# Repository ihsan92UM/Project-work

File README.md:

# Project-work

## Repository Structure
```
Project-work/
├── Graphics/
│   └── Contains all .png used in Markdown files
├── PCB Designs/
│   └── Contains KiCAD files and final JLCPCB Gerber files
├── Programming Guides/
│   └── Contails First-Time Programming setup for DK and Custom Boards
├── STM32U5_codes/
│   └── v1 and v2 Custom Board Codes
└── nRF5340_codes/
    └── nRF5340DK code and Final Custom Board Code

```

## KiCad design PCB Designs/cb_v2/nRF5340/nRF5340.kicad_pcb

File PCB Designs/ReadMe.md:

# PCB Design 

## Repository Structure
```
PCB Designs/
├── JLCPCB_Files/
│   ├── Stencil
│   ├── board1_nrf5340
│   ├── board2_stm32
│   ├── Stencil.zip
│   ├── board1_nrf5340.zip
│   └── board2_stm32.zip	
├── cb_v1/
│   ├── STM32U5
│   └── nRF5340	
├── cb_v2/
│   ├── STM32U5
│   └── nRF5340	
├── Parts_list.xlsx
└── pcb ordering JLCPCB.pdf
```
## Requirement

* [KiCAD 8.0](https://www.kicad.org/download/)

## Production House
* [JLCPCB](https://jlcpcb.com/)
>[!NOTE]
> Follow the [PDF](https://github.com/ihsan92UM/Project-work/blob/359b432a75f67255255755fd50f5ba6b127fc0ec/PCB%20Designs/pcb%20ordering%20JLCPCB.pdf) for ordering manual. Both Custom board uses recomended stackup for 1.6mm diameter with Impedence control.

## Folder Deatils
| Folder | Comments     |
|------------------------------|------------------------------|
|  JLCPCB_Files                    | .zip files are Production files for JLCPCB           |
| cb_v1                 | Sensor Measurement Board (60mm Diameter )          |
| cb_v2          |   Final Custom Board files |
| Parts_list.xlsx                | Remaining components           |

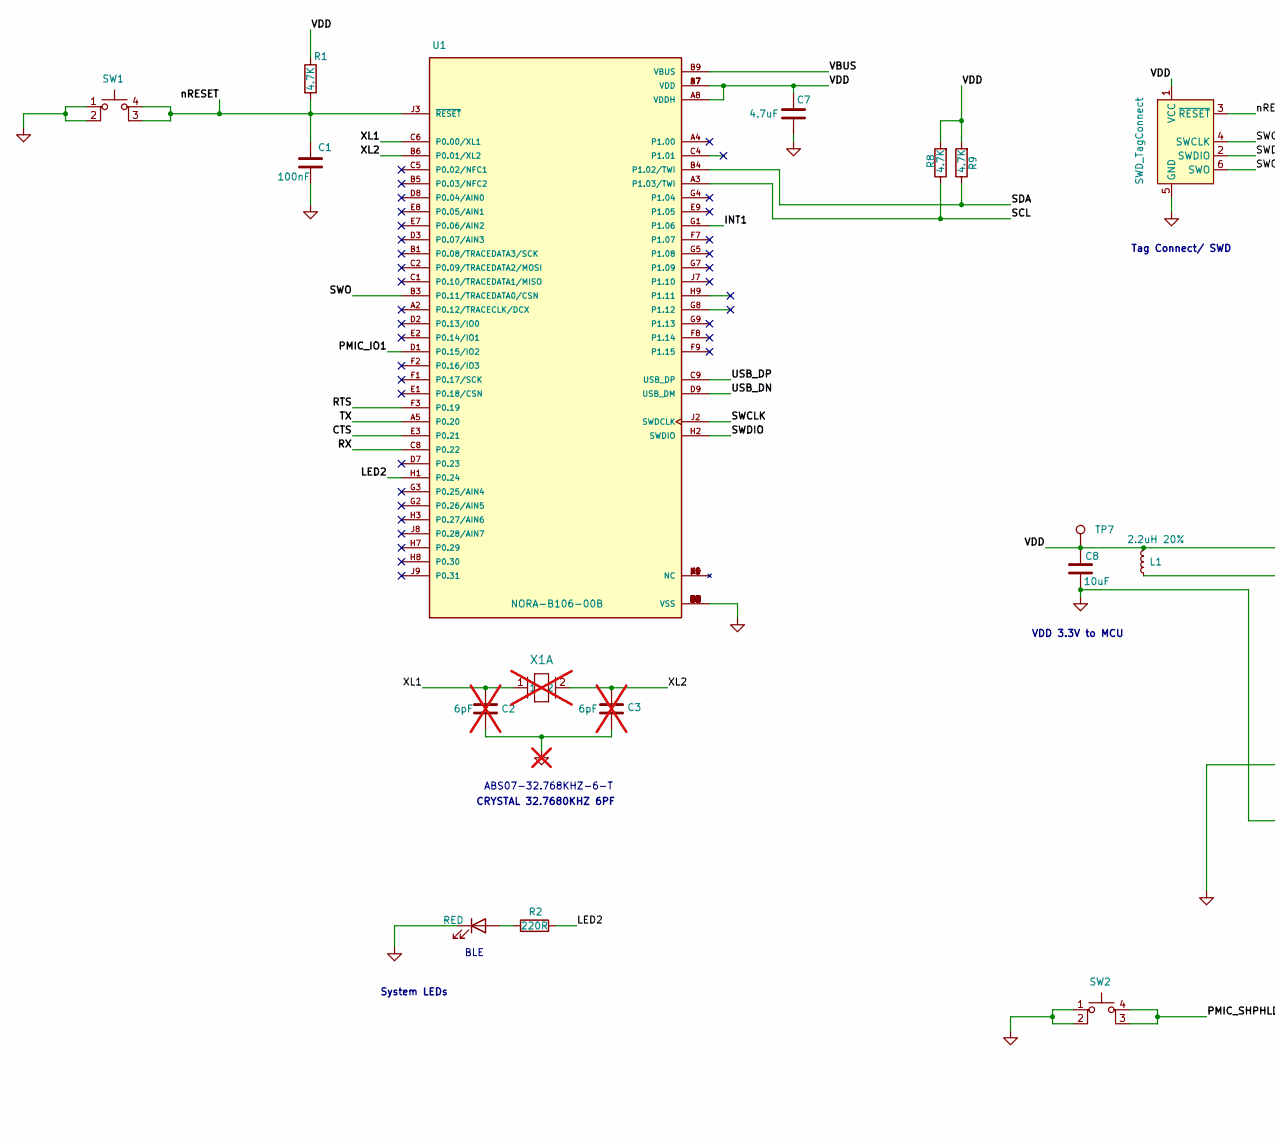
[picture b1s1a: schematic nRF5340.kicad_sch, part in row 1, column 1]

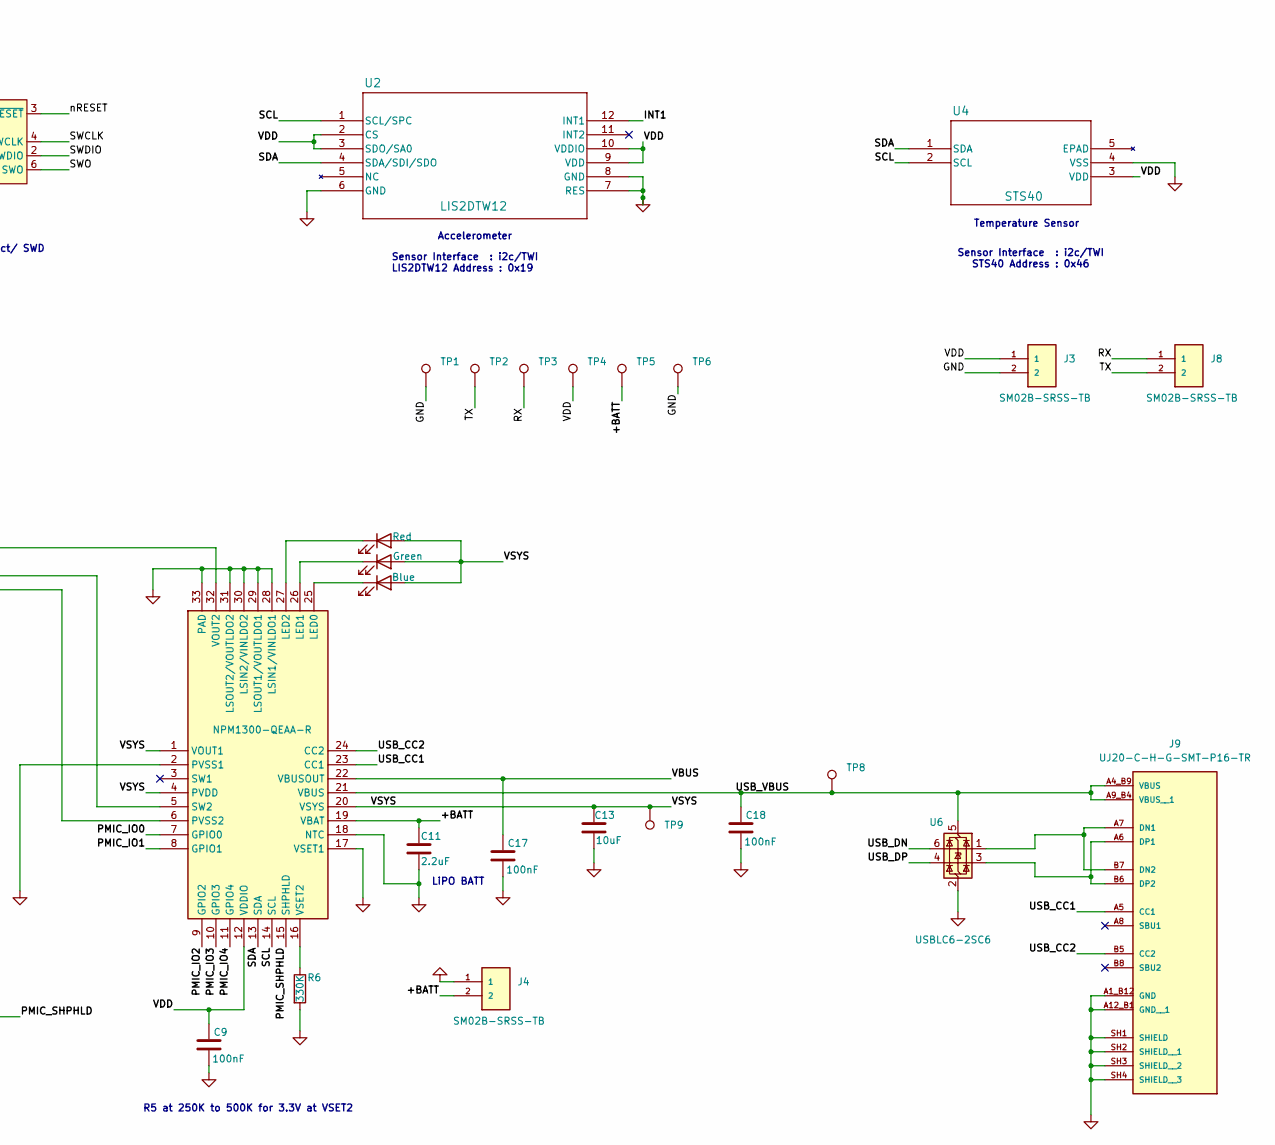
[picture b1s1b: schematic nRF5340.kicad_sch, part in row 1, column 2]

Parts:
C1, C9, C17, C18: 100nF; C_0603_1608Metric
C2, C3: 6pF; C_0603_1608Metric; not fitted
C7: 4.7uF; C_0603_1608Metric
C8, C13: 10uF; C_0603_1608Metric
C11: 2.2uF; C_0603_1608Metric
D1: RED; LED_0603_1608Metric
D3: Red; LED_0603_1608Metric
D4: Green; LED_0603_1608Metric
D5: Blue; LED_0603_1608Metric
IC1: NPM1300-QEAA-R; NPM1300; Manufacturer_Part_Number NPM1300-QEAA-R; Mouser Part Number 949-NPM1300-QEAA-R
J2: SWD_TagConnect; Tag-Connect_TC2030-IDC-NL_2x03_P1.27mm_Vertical
J3, J4, J8: SM02B-SRSS-TB
J9: UJ20-C-H-G-SMT-P16-TR; SAMESKY_UJ20-C-H-G-SMT-P16-TR-USBC-FEMALE; PARTREV 1.0
L1: 2.2uH 20%; L_0603_1608Metric
R1, R8, R9: 4.7K; R_0603_1608Metric
R2: 220R; R_0603_1608Metric
R6: 330K; R_0603_1608Metric
SW1, SW2: SW_MEC_5E; SW4_PTS815 SJM 250 SMTR LFS_CNK
TP1, TP2, TP3, TP4, TP5, TP6: TestPoint; TestPoint_Pad_1.5x1.5mm
TP7, TP9: TestPoint; TestPoint_Pad_D1.0mm
TP8: TestPoint; TestPoint_Pad_D1.5mm
U1: NORA-B106-00B; PARTREV R05
U2: LIS2DTW12; LIS2DTW12_STM
U4: STS40
U6: USBLC6-2SC6; SOT-23-6
X1: ABS07-32.768KHZ-6-T; XTAL_ABS07_ABR; not fitted

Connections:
/+BATT: C11.1, IC1.19 (VBAT), J4.2, TP5.1
/CTS: U1.E3 (P0.21)
/INT1: U1.G1 (P1.06), U2.12 (INT1)
/LED2: R2.2, U1.H1 (P0.24)
/PMIC_IO0: IC1.7 (GPIO0)
/PMIC_IO1: IC1.8 (GPIO1), U1.D1 (P0.15/IO2)
/PMIC_IO2: IC1.9 (GPIO2)
/PMIC_IO3: IC1.10 (GPIO3)
/PMIC_IO4: IC1.11 (GPIO4)
/PMIC_SHPHLD: IC1.15 (SHPHLD), SW2.3 (K), SW2.4 (A)
/RTS: U1.F3 (P0.19)
/RX: J8.1, TP3.1, U1.C8 (P0.22)
/SCL: IC1.14 (SCL), R8.1, U1.A3 (P1.03/TWI), U2.1 (SCL/SPC), U4.2 (SCL)
/SDA: IC1.13 (SDA), R9.1, U1.B4 (P1.02/TWI), U2.4 (SDA/SDI/SDO), U4.1 (SDA)
/SWCLK: J2.4 (SWCLK), U1.J2 (SWDCLK)
/SWDIO: J2.2 (SWDIO), U1.H2 (SWDIO)
/SWO: J2.6 (SWO), U1.B3 (P0.11/TRACEDATA0/CSN)
/TX: J8.2, TP2.1, U1.A5 (P0.20)
/USB_CC1: IC1.23 (CC1), J9.A5 (CC1)
/USB_CC2: IC1.24 (CC2), J9.B5 (CC2)
/USB_DN: U1.D9 (USB_DM), U6.6 (I/O1)
/USB_DP: U1.C9 (USB_DP), U6.4 (I/O2)
/USB_VBUS: C18.1, IC1.21 (VBUS), J9.A4_B9 (VBUS), J9.A9_B4 (VBUS__1), TP8.1, U6.5 (VBUS)
/VBUS: C17.1, IC1.22 (VBUSOUT), U1.B9 (VBUS)
/VDD: C7.1, C8.1, C9.1, IC1.12 (VDDIO), IC1.32 (VOUT2), J2.1 (VCC), J3.1, L1.2, R1.1, R8.2, R9.2, TP4.1, TP7.1, U1.A7 (VDD), U1.A8 (VDDH), U1.B7 (VDD), U2.2 (CS), U2.3 (SDO/SA0), U2.9 (VDD), U2.10 (VDDIO), U4.3 (VDD)
/VSYS: C13.1, D3.2 (A), D4.2 (A), D5.2 (A), IC1.1 (VOUT1), IC1.4 (PVDD), IC1.20 (VSYS), TP9.1
/XL1: C2.1, U1.C6 (P0.00/XL1), X1.1
/XL2: C3.1, U1.B6 (P0.01/XL2), X1.2
/nRESET: C1.1, J2.3 (~RESET), R1.2, SW1.3 (K), SW1.4 (A), U1.J3 (~RESET)
GND: C1.2, C2.2, C3.2, C7.2, C8.2, C9.2, C11.2, C13.2, C17.2, C18.2, D1.1 (K), IC1.2 (PVSS1), IC1.6 (PVSS2), IC1.17 (VSET1), IC1.18 (NTC), IC1.28 (LSIN1/VINLDO1), IC1.29 (LSOUT1/VOUTLDO1), IC1.30 (LSIN2/VINLDO2), IC1.31 (LSOUT2/VOUTLDO2), IC1.33 (PAD), J2.5 (GND), J3.2, J4.1, J9.A1_B12 (GND), J9.A12_B1 (GND__1), J9.SH1 (SHIELD), J9.SH2 (SHIELD__1), J9.SH3 (SHIELD__2), J9.SH4 (SHIELD__3), R6.2, SW1.1, SW1.2, SW2.1, SW2.2, TP1.1, TP6.1, U1.A1 (VSS), U1.A9 (VSS), U1.B2 (VSS), U1.B8 (VSS), U1.E4 (VSS), U1.E5 (VSS), U1.F4 (VSS), U1.F5 (VSS), U1.K2 (VSS), U1.K3 (VSS), U1.K5 (VSS), U1.K7 (VSS), U1.K8 (VSS), U1.L1 (VSS), U1.L9 (VSS), U1.M1 (VSS), U1.M2 (VSS), U1.M8 (VSS), U1.M9 (VSS), U2.6 (GND), U2.7 (RES), U2.8 (GND), U4.4 (VSS), U6.2 (GND)
unnamed: D1.2 (A), R2.1
unnamed: D3.1 (K), IC1.27 (LED2)
unnamed: D4.1 (K), IC1.26 (LED1)
unnamed: D5.1 (K), IC1.25 (LED0)
unnamed: IC1.5 (SW2), L1.1
unnamed: IC1.16 (VSET2), R6.1
unnamed: J9.A7 (DN1), J9.B7 (DN2), U6.1 (I/O1)
unnamed: J9.A6 (DP1), J9.B6 (DP2), U6.3 (I/O2)

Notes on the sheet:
Sensor Interface : i2c/TWI STS40 Address : 0x46
Sensor Interface : i2c/TWI LIS2DTW12 Address : 0x19
LiPO BATT
BLE
Tag Connect/ SWD
CRYSTAL 32.7680KHZ 6PF
Temperature Sensor
System LEDs
R5 at 250K to 500K for 3.3V at VSET2
Accelerometer
ABS07-32.768KHZ-6-T
VDD 3.3V to MCU

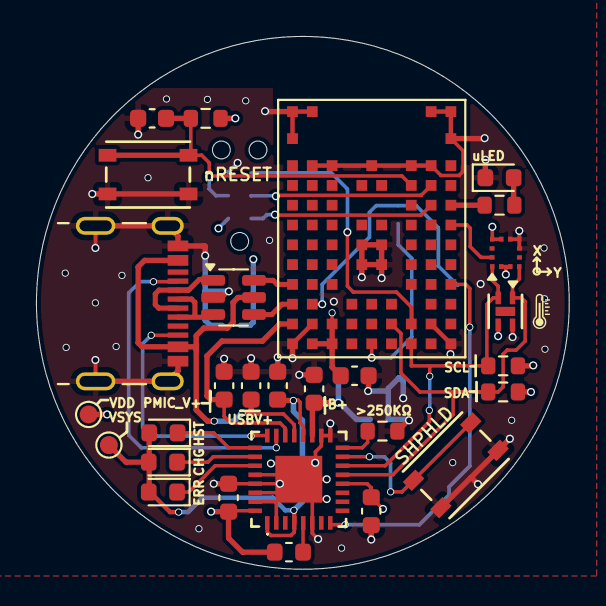
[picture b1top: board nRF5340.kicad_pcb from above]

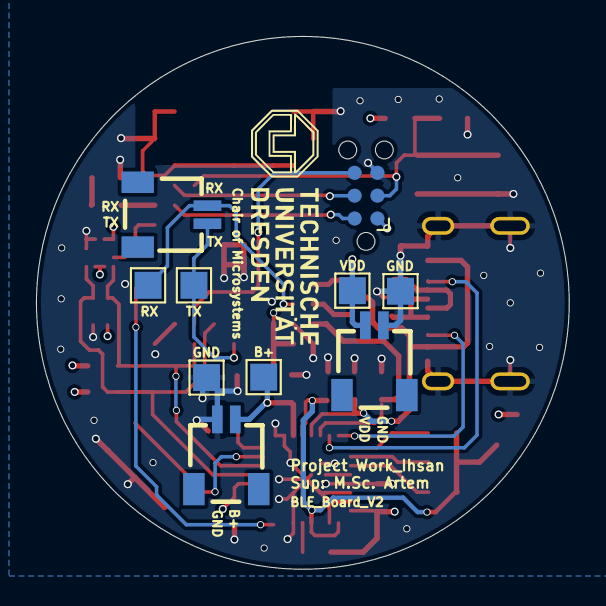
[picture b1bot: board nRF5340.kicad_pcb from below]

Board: 4 copper layers, 29.6 x 29.6 mm, 39 parts (11 on the bottom side), 30 nets.

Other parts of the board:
g: LOGO

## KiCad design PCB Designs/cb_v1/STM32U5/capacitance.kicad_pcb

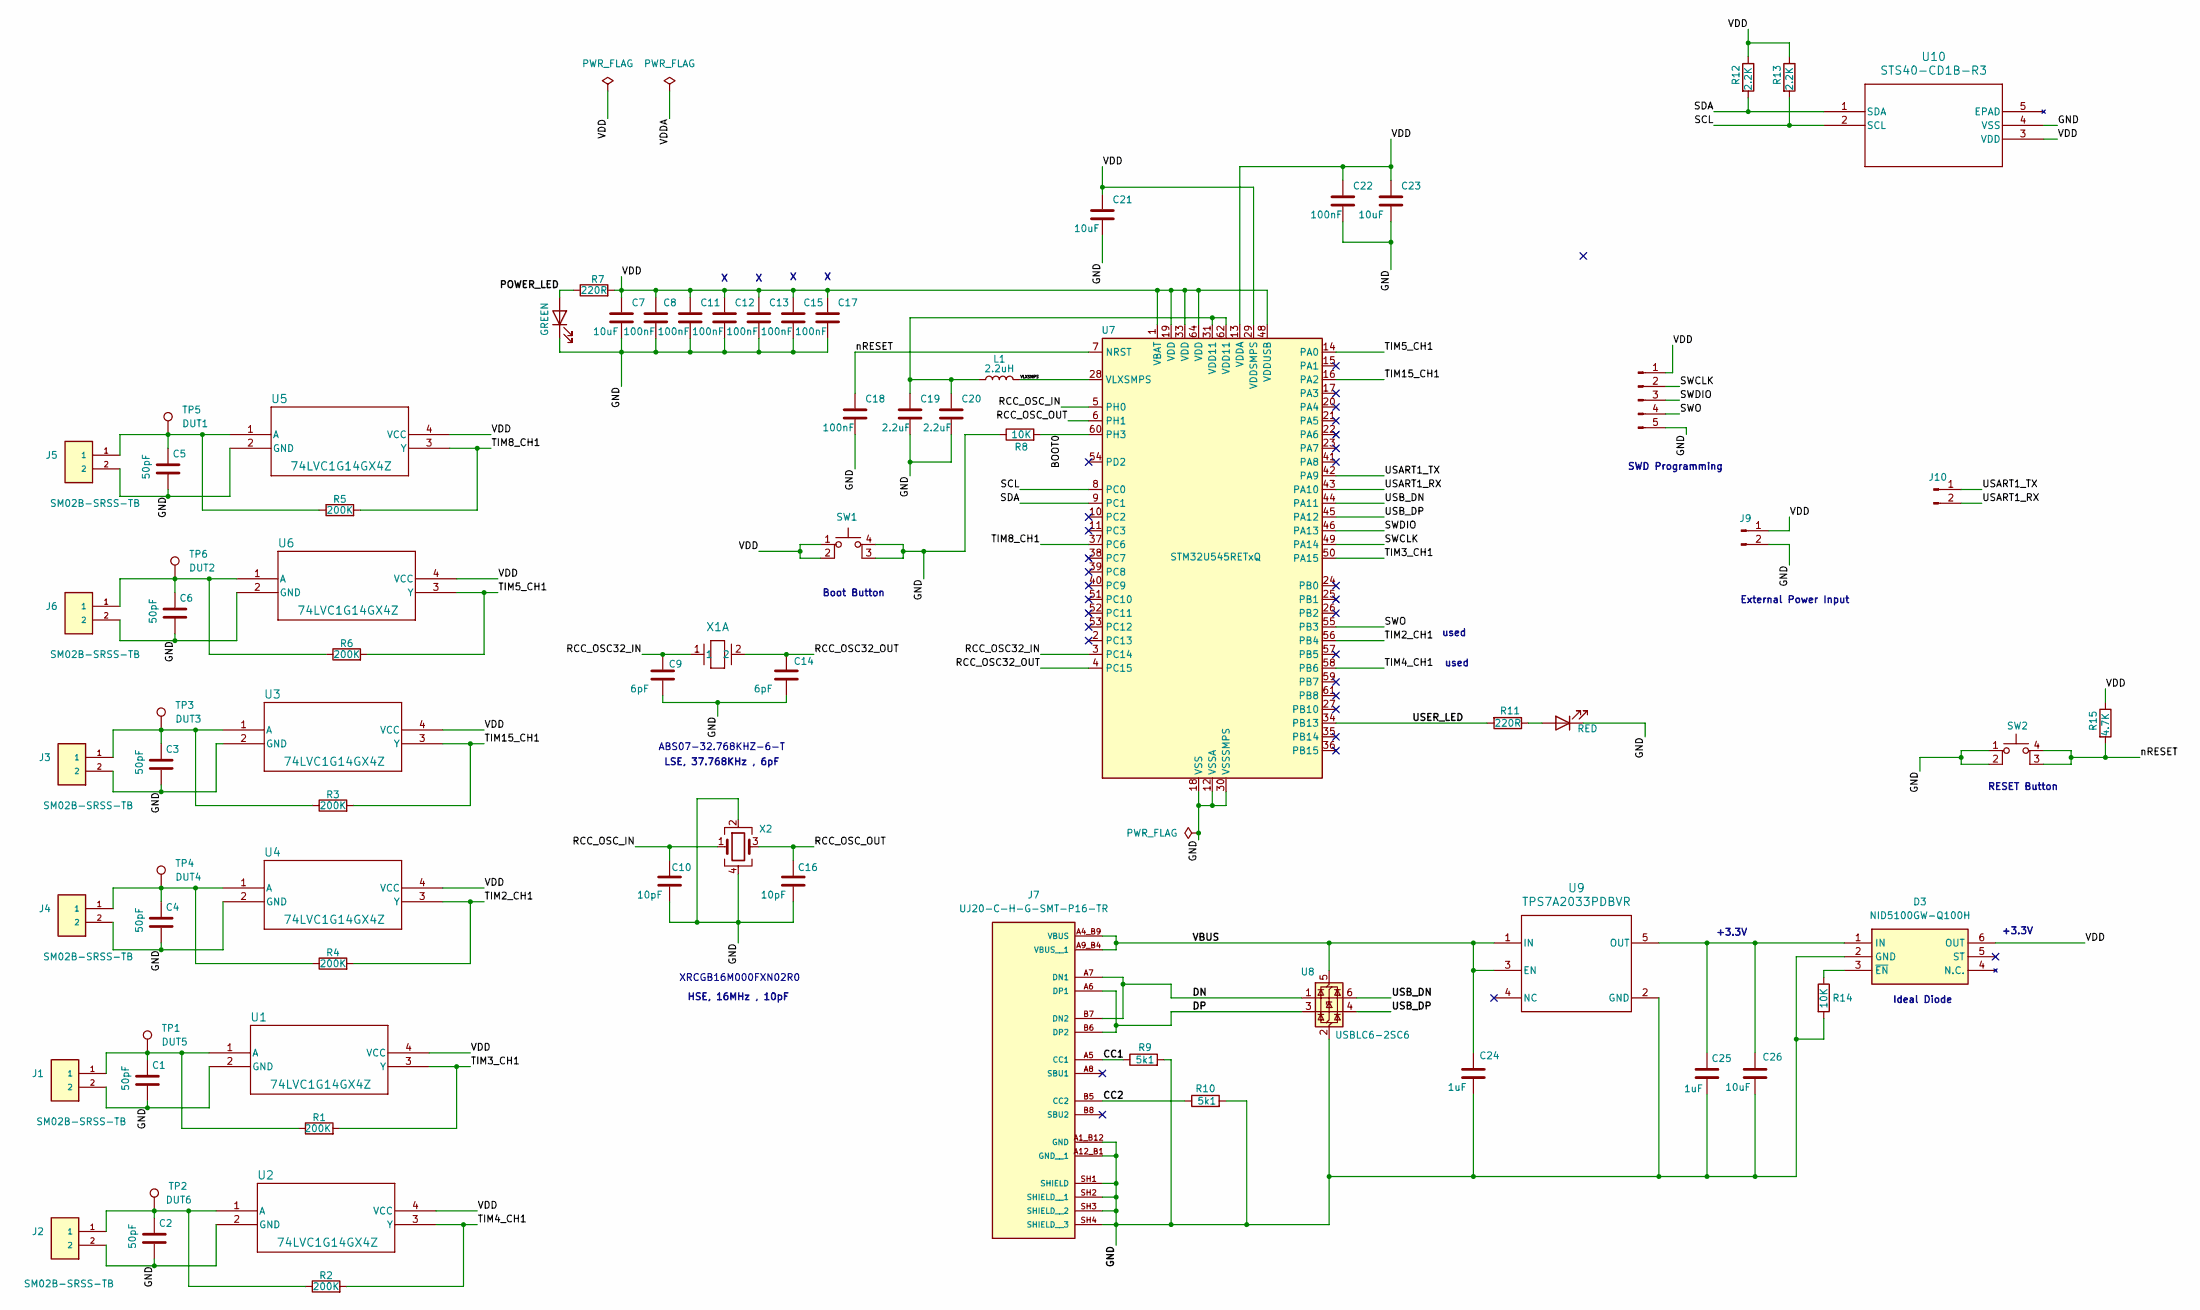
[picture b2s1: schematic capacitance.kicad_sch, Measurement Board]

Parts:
C1, C2, C3, C4, C5, C6: 50pF; C_0603_1608Metric
C7, C21, C23, C26: 10uF; C_0603_1608Metric
C8, C11, C12, C13, C15, C17, C18, C22: 100nF; C_0603_1608Metric
C9, C14: 6pF; C_0603_1608Metric
C10, C16: 10pF; C_0603_1608Metric
C19, C20: 2.2uF; C_0603_1608Metric
C24, C25: 1uF; C_0603_1608Metric
D1: GREEN; LED_0603_1608Metric
D2: RED; LED_0603_1608Metric
D3: NID5100GW-Q100H; SOT65P210X110-6N; Manufacturer_Part_Number NID5100GW-Q100H; Mouser Part Number 771-NID5100GW-Q100H
J1, J2, J3, J4, J5, J6: SM02B-SRSS-TB
J7: UJ20-C-H-G-SMT-P16-TR; SAMESKY_UJ20-C-H-G-SMT-P16-TR-USBC-FEMALE; PARTREV 1.0
J8: Conn_01x05_Pin; PinHeader_1x05_P2.54mm_Vertical
J9, J10: Conn_01x02_Pin; PinHeader_1x02_P2.54mm_Vertical
L1: 2.2uH; L_0603_1608Metric
R1, R2, R3, R4, R5, R6: 200K; R_0603_1608Metric
R7, R11: 220R; R_0603_1608Metric
R8, R14: 10K; R_0603_1608Metric
R9, R10: 5k1; R_0603_1608Metric
R12, R13: 2.2K; R_0603_1608Metric
R15: 4.7K; R_0603_1608Metric
SW1, SW2: SW_MEC_5E; SW4_PTS815 SJM 250 SMTR LFS_CNK
TP1: DUT5; TestPoint_Pad_1.0x1.0mm
TP2: DUT6; TestPoint_Pad_1.0x1.0mm
TP3: DUT3; TestPoint_Pad_1.0x1.0mm
TP4: DUT4; TestPoint_Pad_1.0x1.0mm
TP5: DUT1; TestPoint_Pad_1.0x1.0mm
TP6: DUT2; TestPoint_Pad_1.0x1.0mm
U1, U2, U3, U4, U5, U6: 74LVC1G14GX4Z; X2SON4XP6XP6_NEX
U7: STM32U545RETxQ; LQFP-64_10x10mm_P0.5mm
U8: USBLC6-2SC6; SOT-23-6
U9: TPS7A2033PDBVR
U10: STS40-CD1B-R3; STS40
X1: ABS07-32.768KHZ-6-T; XTAL_ABS07_ABR
X2: Crystal_GND24; ECS-25MHz_XTAL

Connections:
/BOOT0: R8.2, U7.60 (PH3)
/CC1: J7.A5 (CC1), R9.1
/CC2: J7.B5 (CC2), R10.1
/DN: J7.A7 (DN1), J7.B7 (DN2), U8.1 (I/O1)
/DP: J7.A6 (DP1), J7.B6 (DP2), U8.3 (I/O2)
/GND: C1.2, C2.2, C3.2, C4.2, C5.2, C6.2, C7.2, C8.2, C9.2, C10.2, C11.2, C12.2, C13.2, C14.2, C15.2, C16.2, C17.2, C18.2, C19.2, C20.2, C21.2, C22.2, C23.2, C24.2, C25.2, C26.2, D1.1 (K), D2.1 (K), D3.2 (GND), J1.2, J2.2, J3.2, J4.2, J5.2, J6.2, J7.A1_B12 (GND), J7.A12_B1 (GND__1), J7.SH1 (SHIELD), J7.SH2 (SHIELD__1), J7.SH3 (SHIELD__2), J7.SH4 (SHIELD__3), J8.5, J9.2, R8.1, R9.2, R10.2, R14.2, SW1.3 (K), SW1.4 (A), SW2.1, SW2.2, U1.2 (GND), U2.2 (GND), U3.2 (GND), U4.2 (GND), U5.2 (GND), U6.2 (GND), U7.12 (VSSA), U7.18 (VSS), U7.30 (VSSSMPS), U7.32 (VSS), U7.47 (VSS), U7.63 (VSS), U8.2 (GND), U9.2 (GND), U10.4 (VSS), X2.2, X2.4
/POWER_LED: D1.2 (A), R7.1
/RCC_OSC32_IN: C9.1, U7.3 (PC14), X1.1
/RCC_OSC32_OUT: C14.1, U7.4 (PC15), X1.2
/RCC_OSC_IN: C10.1, U7.5 (PH0), X2.1
/RCC_OSC_OUT: C16.1, U7.6 (PH1), X2.3
/SCL: R13.2, U7.8 (PC0), U10.2 (SCL)
/SDA: R12.2, U7.9 (PC1), U10.1 (SDA)
/SWCLK: J8.2, U7.49 (PA14)
/SWDIO: J8.3, U7.46 (PA13)
/SWO: J8.4, U7.55 (PB3)
/TIM2_CH1: R4.2, U4.3 (Y), U7.56 (PB4)
/TIM3_CH1: R1.2, U1.3 (Y), U7.50 (PA15)
/TIM4_CH1: R2.2, U2.3 (Y), U7.58 (PB6)
/TIM5_CH1: R6.2, U6.3 (Y), U7.14 (PA0)
/TIM8_CH1: R5.2, U5.3 (Y), U7.37 (PC6)
/TIM15_CH1: R3.2, U3.3 (Y), U7.16 (PA2)
/USART1_RX: J10.2, U7.43 (PA10)
/USART1_TX: J10.1, U7.42 (PA9)
/USB_DN: U7.44 (PA11), U8.6 (I/O1)
/USB_DP: U7.45 (PA12), U8.4 (I/O2)
/USER_LED: R11.2, U7.34 (PB13)
/VBUS: C24.1, J7.A4_B9 (VBUS), J7.A9_B4 (VBUS__1), U8.5 (VBUS), U9.1 (IN), U9.3 (EN)
/VDD: C7.1, C8.1, C11.1, C12.1, C13.1, C15.1, C17.1, C21.1, C22.1, C23.1, D3.6 (OUT), J8.1, J9.1, R7.2, R12.1, R13.1, R15.1, SW1.1, SW1.2, U1.4 (VCC), U2.4 (VCC), U3.4 (VCC), U4.4 (VCC), U5.4 (VCC), U6.4 (VCC), U7.1 (VBAT), U7.13 (VDDA), U7.19 (VDD), U7.29 (VDDSMPS), U7.33 (VDD), U7.48 (VDDUSB), U7.64 (VDD), U10.3 (VDD)
/VLXSMPS: L1.2, U7.28 (VLXSMPS)
/nRESET: C18.1, R15.2, SW2.3 (K), SW2.4 (A), U7.7 (NRST)
unnamed: C19.1, C20.1, L1.1, U7.31 (VDD11), U7.62 (VDD11)
unnamed: D2.2 (A), R11.1
unnamed: C25.1, C26.1, D3.1 (IN), U9.5 (OUT)
unnamed: D3.3 (~EN), R14.1
unnamed: C1.1, J1.1, R1.1, TP1.1, U1.1 (A)
unnamed: C2.1, J2.1, R2.1, TP2.1, U2.1 (A)
unnamed: C3.1, J3.1, R3.1, TP3.1, U3.1 (A)
unnamed: C4.1, J4.1, R4.1, TP4.1, U4.1 (A)
unnamed: C5.1, J5.1, R5.1, TP5.1, U5.1 (A)
unnamed: C6.1, J6.1, R6.1, TP6.1, U6.1 (A)

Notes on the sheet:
HSE, 16MHz , 10pF
External Power Input
used
SWD Programming
+3.3V
Ideal Diode
LSE, 37.768KHz , 6pF
XRCGB16M000FXN02R0
Boot Button
RESET Button
ABS07-32.768KHZ-6-T

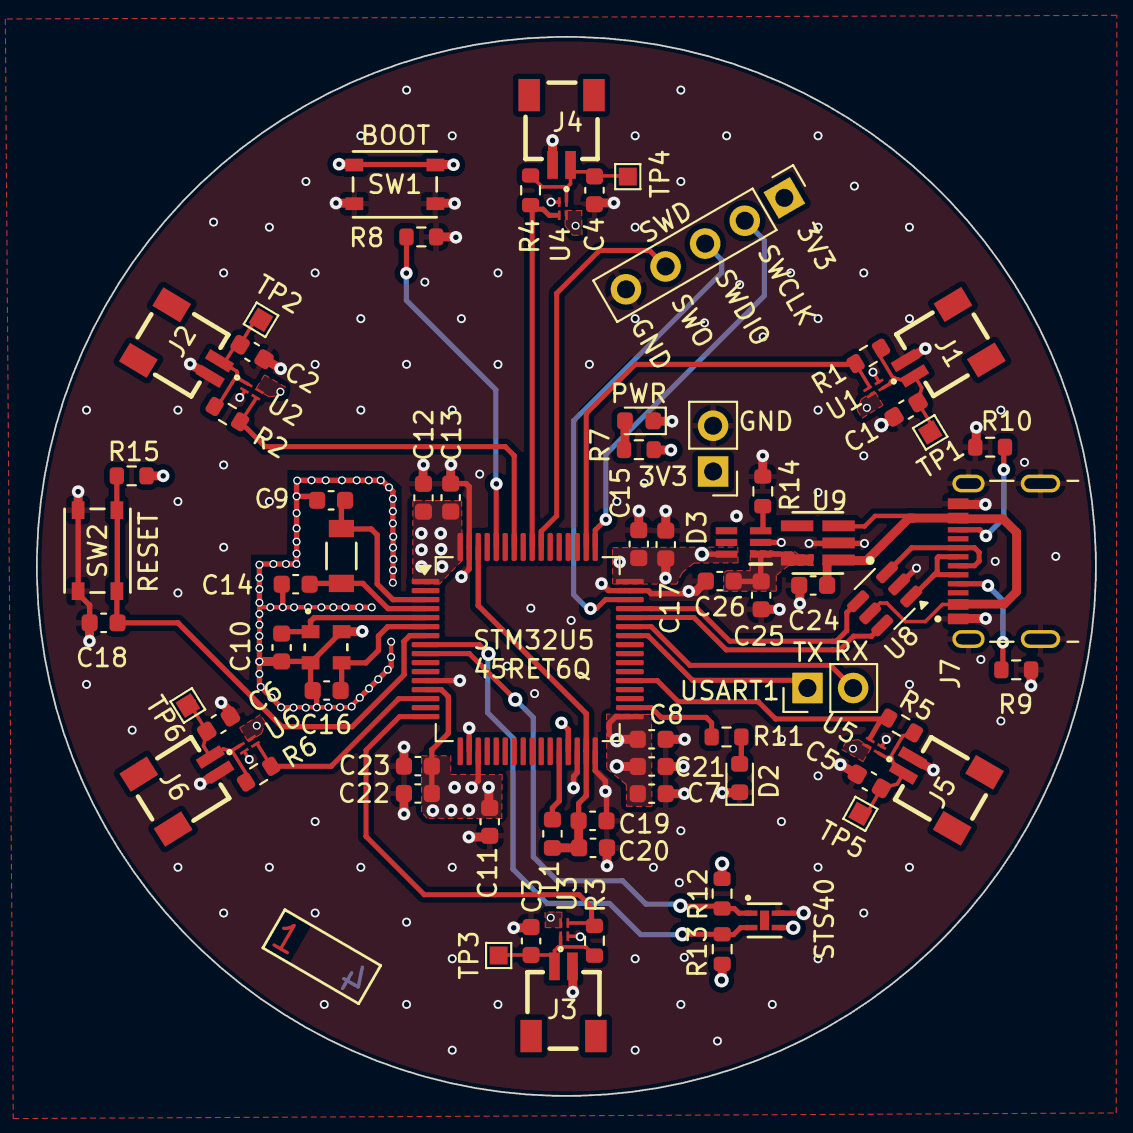
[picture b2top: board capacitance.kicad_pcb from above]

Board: 4 copper layers, 58.8 x 58.8 mm, 75 parts (0 on the bottom side), 41 nets.

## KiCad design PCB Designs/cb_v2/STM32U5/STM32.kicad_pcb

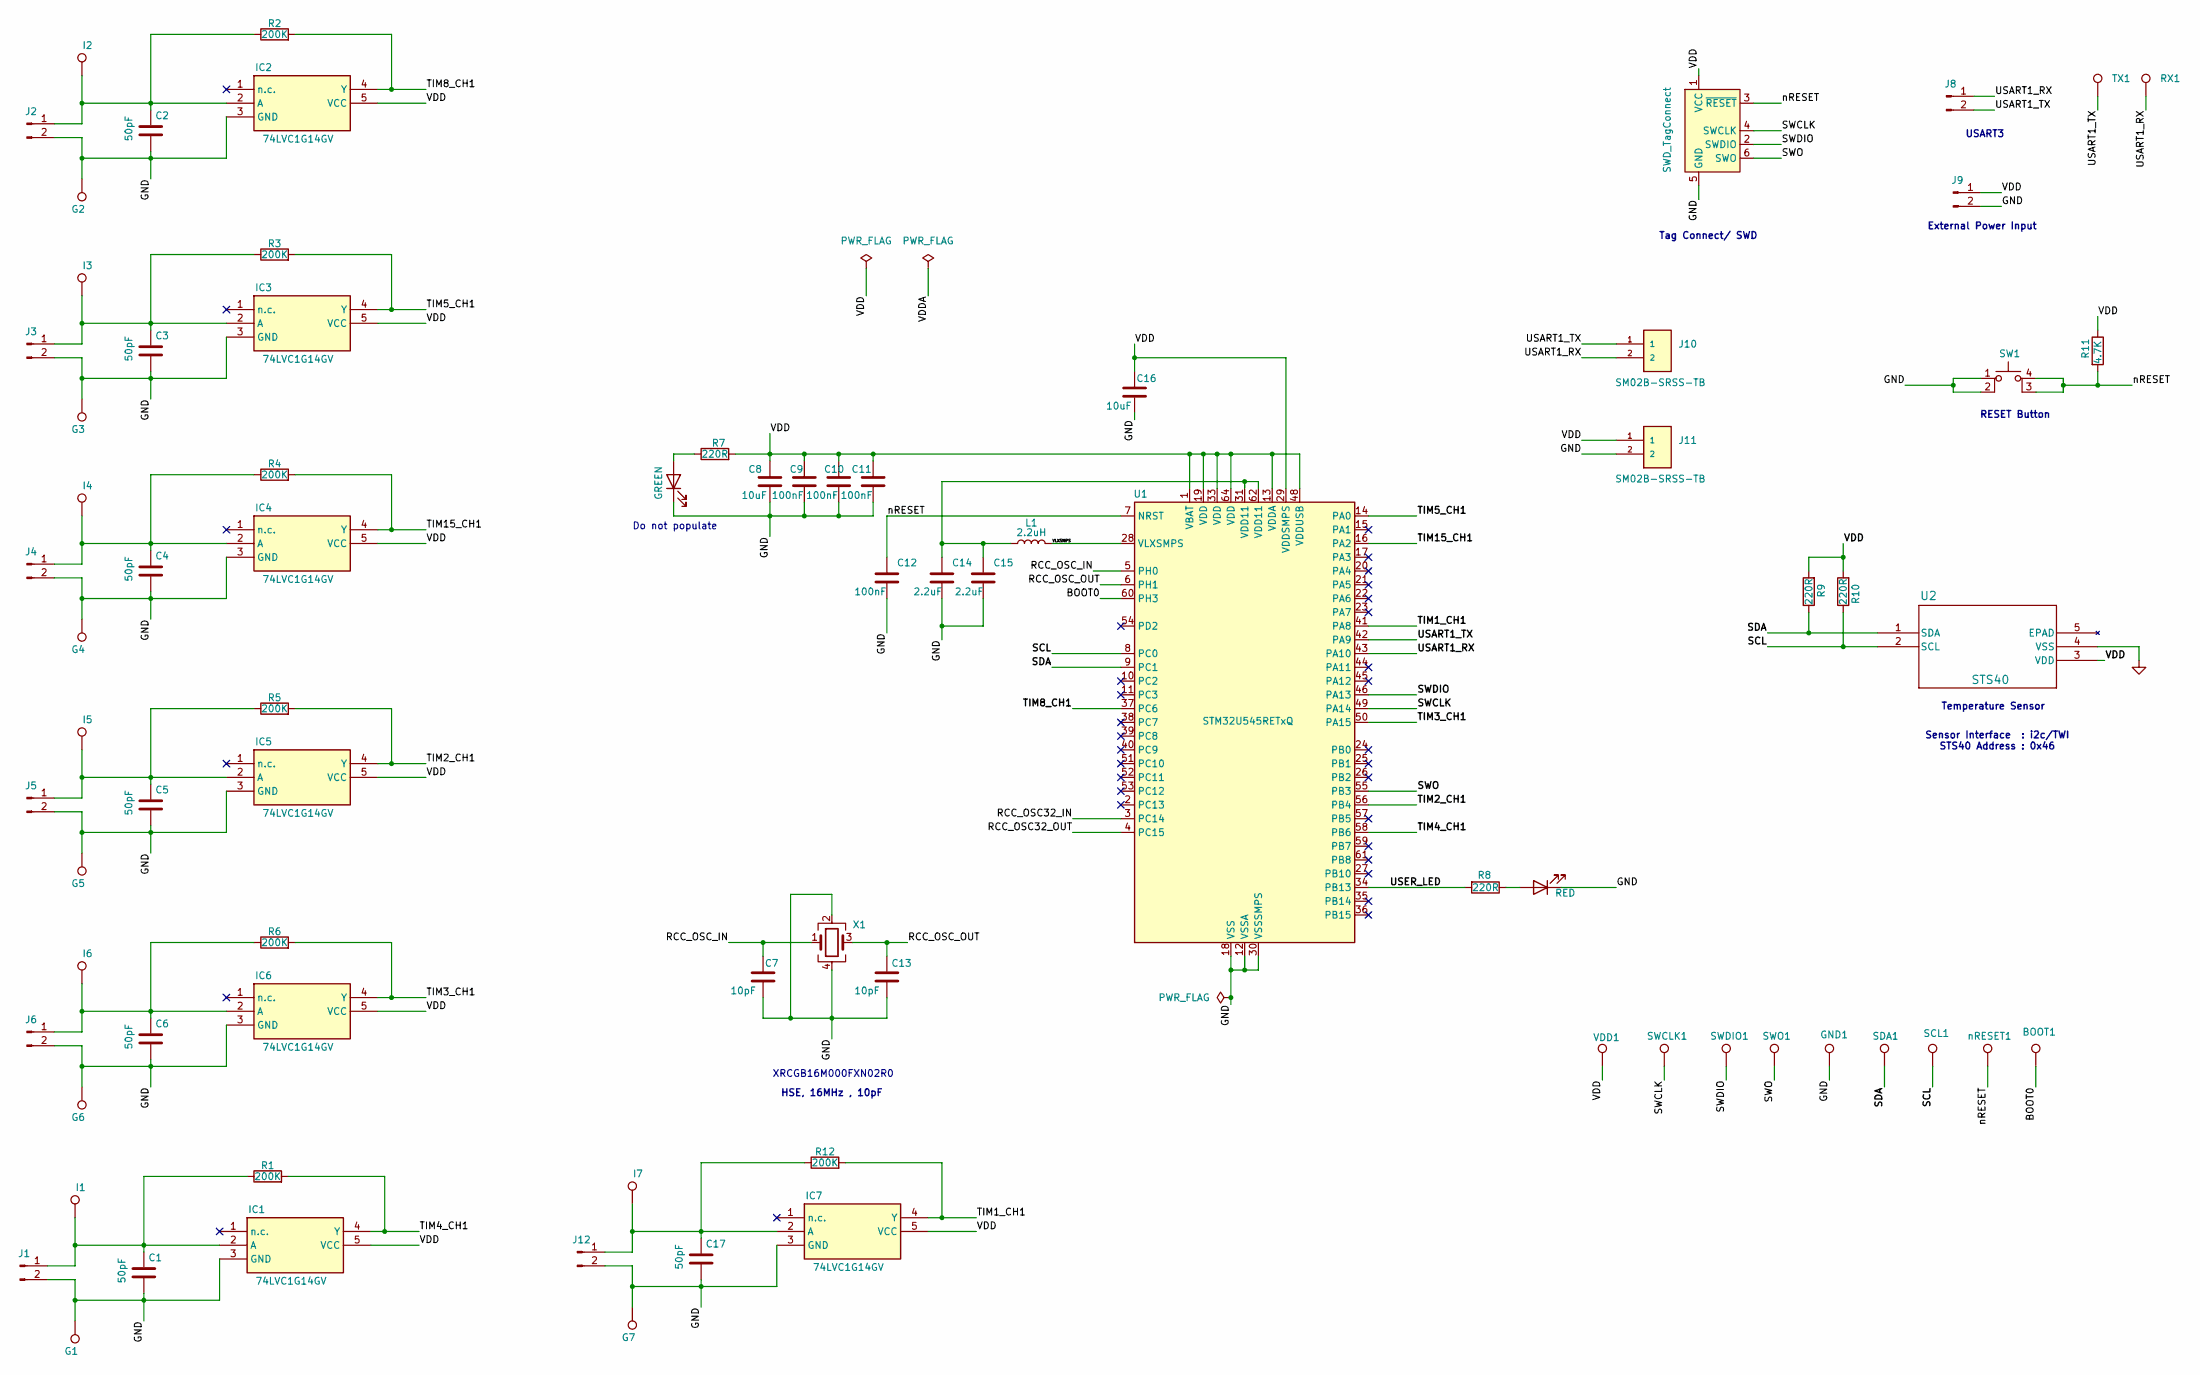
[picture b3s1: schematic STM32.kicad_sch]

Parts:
BOOT1: DUT1; TestPoint_Pad_1.0x1.0mm
C1, C2, C3, C4, C5, C6: 50pF; C_0402_1005Metric
C7, C13: 10pF; C_0402_1005Metric
C8, C16: 10uF; C_0402_1005Metric
C9, C10, C11: 100nF; C_0402_1005Metric
C12: 100nF; R_0603_1608Metric
C14, C15: 2.2uF; C_0402_1005Metric
C17: 50pF; C_0603_1608Metric_Pad1.08x0.95mm_HandSolder
D1: GREEN; LED_0603_1608Metric
D2: RED; LED_0603_1608Metric
G1, G2, G3, G4, G5, G6, G7: DUT1; TestPoint_Pad_1.0x1.0mm
GND1: DUT1; TestPoint_Pad_1.0x1.0mm
I1, I2, I3, I4, I5, I6, I7: DUT1; TestPoint_Pad_1.0x1.0mm
IC1, IC2, IC3, IC4, IC5, IC6, IC7: 74LVC1G14GV; Manufacturer_Part_Number 74LVC1G14GV,125; Mouser Part Number 771-74LVC1G14GV
J1, J2, J3, J4, J5, J6, J8, J9, J12: Conn_01x02_Pin; PinHeader_1x02_P1.27mm_Vertical
J7: SWD_TagConnect; Tag-Connect_TC2030-IDC-NL_2x03_P1.27mm_Vertical
J10, J11: SM02B-SRSS-TB
L1: 2.2uH; L_0603_1608Metric
R1, R2, R3, R4, R5, R6: 200K; R_0402_1005Metric
R7: 220R; R_0603_1608Metric
R8, R9, R10: 220R; R_0402_1005Metric
R11: 4.7K; R_0603_1608Metric
R12: 200K; R_0603_1608Metric_Pad0.98x0.95mm_HandSolder
RX1: DUT1; TestPoint_Pad_1.0x1.0mm
SCL1: DUT1; TestPoint_Pad_1.0x1.0mm
SDA1: DUT1; TestPoint_Pad_1.0x1.0mm
SW1: SW_MEC_5E; SW4_PTS815 SJM 250 SMTR LFS_CNK
SWCLK1: DUT1; TestPoint_Pad_1.0x1.0mm
SWDIO1: DUT1; TestPoint_Pad_1.0x1.0mm
SWO1: DUT1; TestPoint_Pad_1.0x1.0mm
TX1: DUT1; TestPoint_Pad_1.0x1.0mm
U1: STM32U545RETxQ; LQFP-64_10x10mm_P0.5mm
U2: STS40
VDD1: DUT1; TestPoint_Pad_1.0x1.0mm
X1: Crystal_GND24; ECS-25MHz_XTAL
nRESET1: DUT1; TestPoint_Pad_1.0x1.0mm

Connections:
/BOOT0: BOOT1.1, U1.60 (PH3); also elsewhere on the board
/RCC_OSC32_IN: U1.3 (PC14)
/RCC_OSC32_OUT: U1.4 (PC15)
/RCC_OSC_IN: C7.1, U1.5 (PH0), X1.1
/RCC_OSC_OUT: C13.1, U1.6 (PH1), X1.3
/SCL: R10.1, SCL1.1, U1.8 (PC0), U2.2 (SCL); also elsewhere on the board
/SDA: R9.1, SDA1.1, U1.9 (PC1), U2.1 (SDA); also elsewhere on the board
/SWCLK: J7.4 (SWCLK), SWCLK1.1, U1.49 (PA14)
/SWDIO: J7.2 (SWDIO), SWDIO1.1, U1.46 (PA13)
/SWO: J7.6 (SWO), SWO1.1, U1.55 (PB3)
/TIM1_CH1: IC7.4 (Y), R12.2, U1.41 (PA8)
/TIM2_CH1: IC5.4 (Y), R5.2, U1.56 (PB4)
/TIM3_CH1: IC6.4 (Y), R6.2, U1.50 (PA15)
/TIM4_CH1: IC1.4 (Y), R1.2, U1.58 (PB6)
/TIM5_CH1: IC3.4 (Y), R3.2, U1.14 (PA0)
/TIM8_CH1: IC2.4 (Y), R2.2, U1.37 (PC6)
/TIM15_CH1: IC4.4 (Y), R4.2, U1.16 (PA2)
/USART1_RX: J8.1, J10.2, RX1.1, U1.43 (PA10); also elsewhere on the board
/USART1_TX: J8.2, J10.1, TX1.1, U1.42 (PA9); also elsewhere on the board
/USER_LED: R8.2, U1.34 (PB13)
/VDD: C8.1, C9.1, C10.1, C11.1, C16.1, IC1.5 (VCC), IC2.5 (VCC), IC3.5 (VCC), IC4.5 (VCC), IC5.5 (VCC), IC6.5 (VCC), IC7.5 (VCC), J7.1 (VCC), J9.1, J11.1, R7.2, R9.2, R10.2, R11.1, U1.1 (VBAT), U1.13 (VDDA), U1.19 (VDD), U1.29 (VDDSMPS), U1.33 (VDD), U1.48 (VDDUSB), U1.64 (VDD), U2.3 (VDD), VDD1.1; also elsewhere on the board
/VLXSMPS: L1.2, U1.28 (VLXSMPS)
/nRESET: C12.1, J7.3 (~RESET), R11.2, SW1.3 (K), SW1.4 (A), U1.7 (NRST), nRESET1.1; also elsewhere on the board
GND: C1.2, C2.2, C3.2, C4.2, C5.2, C6.2, C7.2, C8.2, C9.2, C10.2, C11.2, C12.2, C13.2, C14.2, C15.2, C16.2, C17.2, D1.1 (K), D2.1 (K), G1.1, G2.1, G3.1, G4.1, G5.1, G6.1, G7.1, GND1.1, IC1.3 (GND), IC2.3 (GND), IC3.3 (GND), IC4.3 (GND), IC5.3 (GND), IC6.3 (GND), IC7.3 (GND), J1.2, J2.2, J3.2, J4.2, J5.2, J6.2, J7.5 (GND), J9.2, J11.2, J12.2, SW1.1, SW1.2, U1.12 (VSSA), U1.18 (VSS), U1.30 (VSSSMPS), U1.32 (VSS), U1.47 (VSS), U1.63 (VSS), U2.4 (VSS), X1.2, X1.4; also elsewhere on the board
unnamed: C14.1, C15.1, L1.1, U1.31 (VDD11), U1.62 (VDD11)
unnamed: D1.2 (A), R7.1
unnamed: D2.2 (A), R8.1
unnamed: C1.1, I1.1, IC1.2 (A), J1.1, R1.1
unnamed: C2.1, I2.1, IC2.2 (A), J2.1, R2.1
unnamed: C3.1, I3.1, IC3.2 (A), J3.1, R3.1
unnamed: C4.1, I4.1, IC4.2 (A), J4.1, R4.1
unnamed: C5.1, I5.1, IC5.2 (A), J5.1, R5.1
unnamed: C6.1, I6.1, IC6.2 (A), J6.1, R6.1
unnamed: C17.1, I7.1, IC7.2 (A), J12.1, R12.1

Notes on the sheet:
XRCGB16M000FXN02R0
External Power Input
Sensor Interface : i2c/TWI STS40 Address : 0x46
RESET Button
Tag Connect/ SWD
HSE, 16MHz , 10pF
USART3
Do not populate
Temperature Sensor

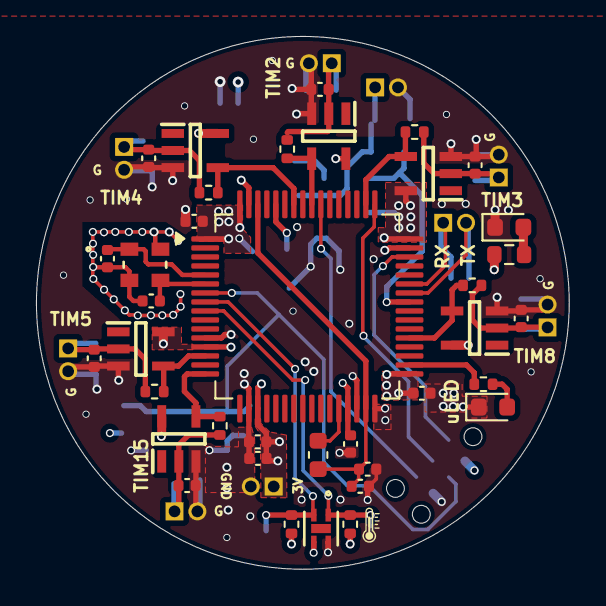
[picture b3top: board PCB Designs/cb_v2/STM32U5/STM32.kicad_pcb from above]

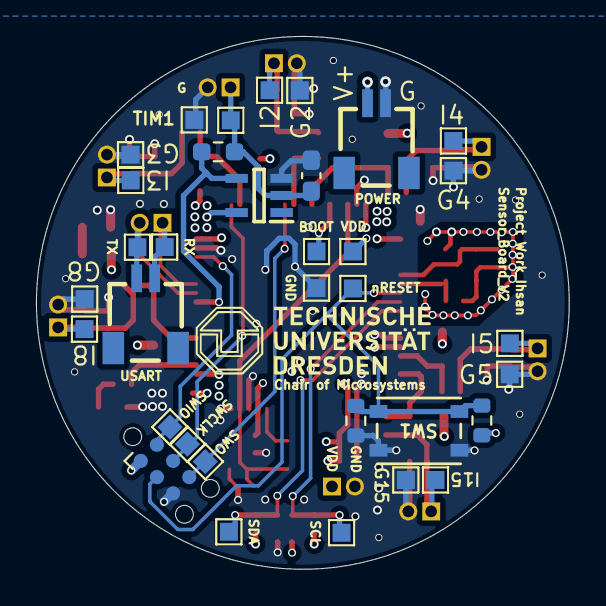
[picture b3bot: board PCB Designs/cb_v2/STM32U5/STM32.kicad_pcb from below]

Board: 4 copper layers, 29.6 x 29.6 mm, 81 parts (36 on the bottom side), 32 nets.

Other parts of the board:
BOOT: DUT1; TestPoint_Pad_1.0x1.0mm
GND: DUT1; TestPoint_Pad_1.0x1.0mm
RX: DUT1; TestPoint_Pad_1.0x1.0mm
SCL: DUT1; TestPoint_Pad_1.0x1.0mm
SDA: DUT1; TestPoint_Pad_1.0x1.0mm
TX: DUT1; TestPoint_Pad_1.0x1.0mm
VDD: DUT1; TestPoint_Pad_1.0x1.0mm
g: LOGO
nRESET: DUT1; TestPoint_Pad_1.0x1.0mm

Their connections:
/BOOT0: BOOT.1; also elsewhere on the board
/SCL: SCL.1; also elsewhere on the board
/SDA: SDA.1; also elsewhere on the board
/USART1_RX: RX.1; also elsewhere on the board
/USART1_TX: TX.1; also elsewhere on the board
/VDD: VDD.1; also elsewhere on the board
/nRESET: nRESET.1; also elsewhere on the board
GND: GND.1; also elsewhere on the board

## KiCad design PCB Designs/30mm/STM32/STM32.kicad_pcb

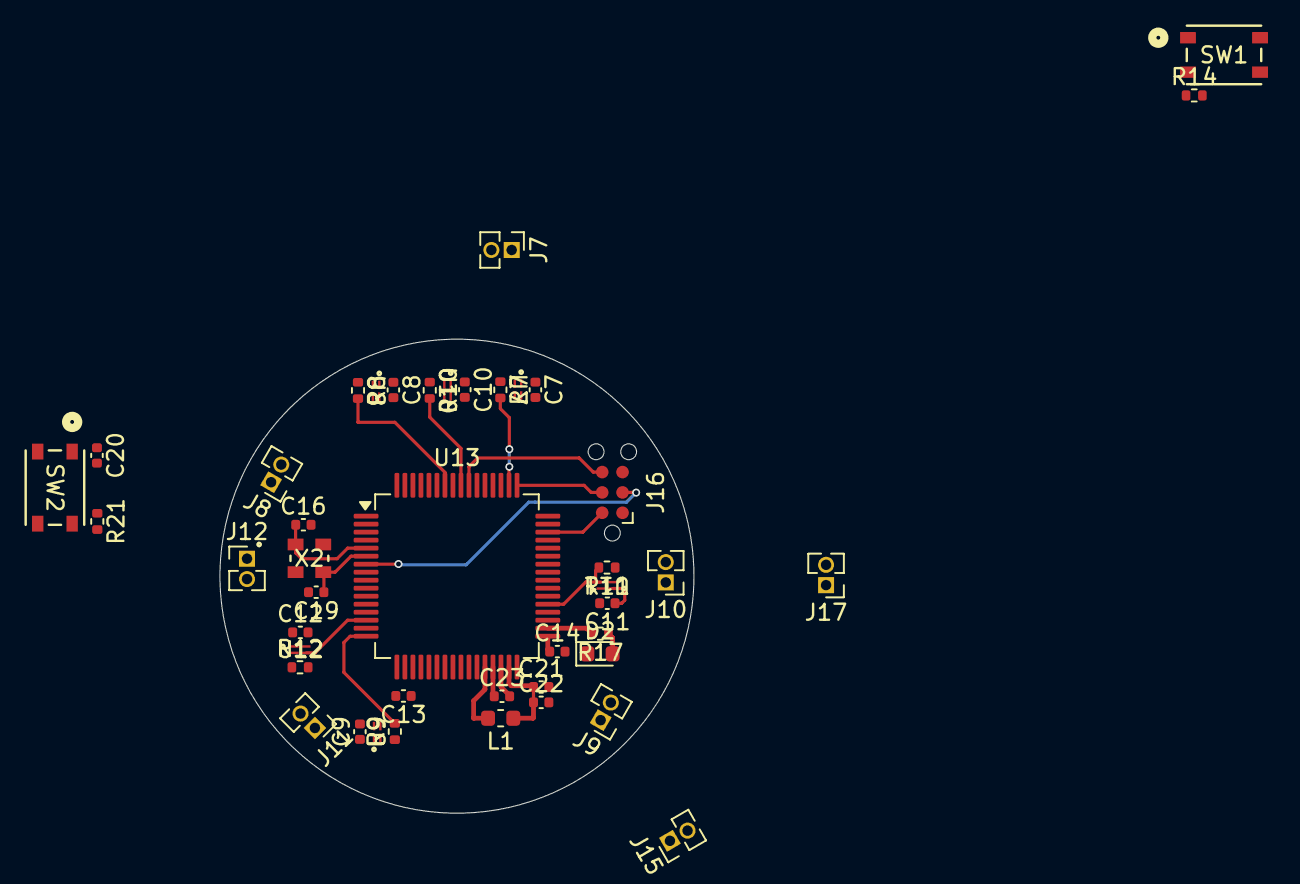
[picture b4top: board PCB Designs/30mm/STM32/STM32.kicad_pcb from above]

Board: 4 copper layers, 29.6 x 29.6 mm, 44 parts (0 on the bottom side), 27 nets.

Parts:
C7, C8, C9, C10, C11, C12: 50pF; C_0402_1005Metric
C13, C23: 10uF; C_0402_1005Metric
C14, C20: 100nF; C_0402_1005Metric
C16, C19: 10pF; C_0402_1005Metric
C21, C22: 2.2uF; C_0402_1005Metric
D2: RED; LED_0603_1608Metric
J7, J8, J9, J10, J11, J12, J15, J17: Conn_01x02_Pin; PinHeader_1x02_P1.27mm_Vertical
J16: SWD_TagConnect; Tag-Connect_TC2030-IDC-NL_2x03_P1.27mm_Vertical
L1: 2.2uH; L_0603_1608Metric
R7, R8, R9, R10, R11, R12: 200K; R_0402_1005Metric
R14: 10K; R_0402_1005Metric
R17: 220R; R_0402_1005Metric
R21: 4.7K; R_0402_1005Metric
SW1, SW2: SW_MEC_5E; SW4_PTS815 SJM 250 SMTR LFS_CNK
U7, U8, U9, U10, U11, U12: 74LVC1G14GX4Z; X2SON4XP6XP6_NEX
U13: STM32U545RETxQ; LQFP-64_10x10mm_P0.5mm
X2: Crystal_GND24; ECS-25MHz_XTAL

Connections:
/BOOT0: R14.2, U13.60 (PH3)
/GND: C7.2, C8.2, C9.2, C10.2, C11.2, C12.2, C13.2, C14.2, C16.2, C19.2, C20.2, C21.2, C22.2, C23.2, D2.1 (K), J7.2, J8.2, J9.2, J10.2, J11.2, J12.2, J15.2, J16.5 (GND), R14.1, SW1.3 (K), SW1.4 (A), SW2.1, SW2.2, U7.2 (GND), U8.2 (GND), U9.2 (GND), U10.2 (GND), U11.2 (GND), U12.2 (GND), U13.12 (VSSA), U13.18 (VSS), U13.30 (VSSSMPS), U13.32 (VSS), U13.47 (VSS), U13.63 (VSS), X2.2, X2.4
/RCC_OSC_IN: C16.1, U13.5 (PH0), X2.1
/RCC_OSC_OUT: C19.1, U13.6 (PH1), X2.3
/SWCLK: J16.4 (SWCLK), U13.49 (PA14)
/SWDIO: J16.2 (SWDIO), U13.46 (PA13)
/SWO: J16.6 (SWO), U13.55 (PB3)
/TIM2_CH1: R10.2, U10.3 (Y), U13.56 (PB4)
/TIM3_CH1: R7.2, U7.3 (Y), U13.50 (PA15)
/TIM4_CH1: R8.2, U8.3 (Y), U13.58 (PB6)
/TIM5_CH1: R12.2, U12.3 (Y), U13.14 (PA0)
/TIM8_CH1: R11.2, U11.3 (Y), U13.37 (PC6)
/TIM15_CH1: R9.2, U9.3 (Y), U13.16 (PA2)
/USART1_RX: J17.2, U13.43 (PA10)
/USART1_TX: J17.1, U13.42 (PA9)
/USER_LED: R17.2, U13.34 (PB13)
/VDD: C13.1, C14.1, C23.1, J15.1, J16.1 (VCC), R21.1, SW1.1, SW1.2, U7.4 (VCC), U8.4 (VCC), U9.4 (VCC), U10.4 (VCC), U11.4 (VCC), U12.4 (VCC), U13.1 (VBAT), U13.13 (VDDA), U13.19 (VDD), U13.29 (VDDSMPS), U13.33 (VDD), U13.48 (VDDUSB), U13.64 (VDD)
/VLXSMPS: L1.2, U13.28 (VLXSMPS)
/nRESET: C20.1, J16.3 (~RESET), R21.2, SW2.3 (K), SW2.4 (A), U13.7 (NRST)
unnamed: C21.1, C22.1, L1.1, U13.31 (VDD11), U13.62 (VDD11)
unnamed: D2.2 (A), R17.1
unnamed: C11.1, J7.1, R11.1, U11.1 (A)
unnamed: C12.1, J8.1, R12.1, U12.1 (A)
unnamed: C7.1, J9.1, R7.1, U7.1 (A)
unnamed: C8.1, J10.1, R8.1, U8.1 (A)
unnamed: C9.1, J11.1, R9.1, U9.1 (A)
unnamed: C10.1, J12.1, R10.1, U10.1 (A)

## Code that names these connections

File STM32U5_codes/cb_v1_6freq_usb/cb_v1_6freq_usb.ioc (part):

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Mcu.Name=STM32U545RETxQ
Mcu.Package=LQFP64
Mcu.UserName=STM32U545RETxQ
PA0.Signal=S_TIM5_CH1
PA10.Mode=Asynchronous
PA10.Signal=USART1_RX
PA11.Mode=Device
PA11.Signal=USB_DM
PA12.Mode=Device
PA12.Signal=USB_DP
PA13\ (JTMS/SWDIO).Mode=Trace_Asynchronous_SW
PA13\ (JTMS/SWDIO).Signal=DEBUG_JTMS-SWDIO
PA14\ (JTCK/SWCLK).Mode=Trace_Asynchronous_SW
PA14\ (JTCK/SWCLK).Signal=DEBUG_JTCK-SWCLK
PA15\ (JTDI).Signal=S_TIM2_CH1
PA2.Signal=S_TIM15_CH1
PA9.Mode=Asynchronous
PA9.Signal=USART1_TX
PB13.GPIOParameters=PinState
PB13.PinState=GPIO_PIN_SET
PB13.Signal=GPIO_Output
PB3\ (JTDO/TRACESWO).Mode=Trace_Asynchronous_SW
PB3\ (JTDO/TRACESWO).Signal=DEBUG_JTDO-SWO
PB4\ (NJTRST).Signal=S_TIM3_CH1
PB6.Signal=S_TIM4_CH1
PC0.Mode=I2C
PC0.Signal=I2C3_SCL
PC1.Mode=I2C
PC1.Signal=I2C3_SDA
PC6.Signal=S_TIM8_CH1
PH0-OSC_IN\ (PH0).Mode=HSE-External-Oscillator
PH0-OSC_IN\ (PH0).Signal=RCC_OSC_IN
PH1-OSC_OUT\ (PH1).Mode=HSE-External-Oscillator
PH1-OSC_OUT\ (PH1).Signal=RCC_OSC_OUT
RCC.HSE_VALUE=16000000
RCC.SYSCLKFreq_VALUE=160000000
RCC.SYSCLKSource=RCC_SYSCLKSOURCE_PLLCLK
board=custom
